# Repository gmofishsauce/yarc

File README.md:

# YARC - Yet Another Retro Computer

## Overview

YARC is a homebrew CPU and computer design implemented in a retro style.
Work on YARC started in April 2021. The initial concept was an 8-bit
computer with a 16-bit multiplexed address/data bus and extensive
pipelining.

In December 2021, the design changed to a 16-bit computer with separate
address and data busses, minimal pipelining, four general registers, an
8-bit-wide/2-cycle ALU, and two hardware stacks. In short, a general
register machine with specific concessions to the efficient implementation
of Charles Moore's FORTH programming language.

Most recently, I decided not to build the stack hardware and to instead
focus on developing the basic instruction set using two of the four
registers for PC and SP. I plan to write a translator for a small subset
of web assembler to YARC machine language (an "AoT" in their terminology,
ahead-of-time compiler). This will allow me to program the YARC in a small
subset any language that can target WASM--like Gnu C or Golang--rather
than confining YARC programming to the Forth language.

YARC is permanently tethered to a host computer (Mac) through a module
called the "Downloader" (a misnomer, because communication is supported
in both directions between host and YARC). The Downloader is based on a
modern microprocessor (Arduino Nano) which implements serial over USB.

The YARC itself is built from 74HC-series CMOS parts, with a few
out-of-period extensions like 8kx8 static CMOS RAMs.

## NRR - It's Not Really Retro

YARC's architecture resembles the [Data General Nova](https://en.wikipedia.org/wiki/Data_General_Nova) minicomputer. The Nova was introduced in 1969. YARC, like Nova, is mostly built from 7400-series components.

But the YARC is _nothing_ like a 1970s minicomputer. Why not? Let me count the ways...

* **Sophisticated open source design software.** In 1969, "design software" meant a sharp pencil, a [plastic template](https://www.amazon.com/Alvin-TD1279-Electric-Electronic-Template/dp/B000KNLR4A/ref=asc_df_B000KNLR4A/), and an angled table. Now, it means [KiCad](https://www.kicad.org/).
* **Highly integrated, sub-100ns static RAMs.** In 1969, semiconductor memory hadn't happened yet. YARC relies on 8k x 8 static CMOS RAMs with 55ns access times - each chip contains more transistors than an _entire_ Data General Nova. And the original Nova, with core memory, had a 5-microsecond cycle time - about 10x slower than YARC can likely achieve.
* **Universal knowledge base.** In 1969, knowledge about computer design was in the hands of a few experts. Today, a quick search can bring you [this](https://www.godevtool.com/GoasmHelp/usflags.htm) or [this](https://www.righto.com/2013/09/the-z-80-has-4-bit-alu-heres-how-it.html).
* **These aren't the 7400 series components you're looking for.** YARC is built with 74HC-series components. These have better noise margins, controlled edge rates, and far lower power consumption than traditional 7400-series TTL. It's fair to say the 74HC-series wasn't introduced until it was already obsolete!

## What's here?

### [ard](https://github.com/gmofishsauce/yarc/tree/main/ard/yarc_fw) - Arduino code for YARC downloader

Nano IDE (v2.X) project holding C++ code for the Arduino that implements
the "Downloader" (which should be renamed to "System Interface" or something).

### [doc](https://github.com/gmofishsauce/yarc/tree/main/doc) - YARC documentation

Engineering documentation for YARC. No "user documentation" is planned,
but some of the documentation is tersely user-oriented, such as the
document that describes the assembly language.

### [ftz](https://github.com/gmofishsauce/yarc/tree/main/ftz) - Fritz sketches for YARC.

Fritzing is a useful sketchpad for breadboard-based designs but it's
incredibly quirky.  No guarantees anyone will be able to load these
sketches, not to mention modify them.

Fritzing really, *really* wants everything in "``~/Documents/Fritzing``" on
Mac, and on Mac, setting $HOME does not affect the expansion of tilde.
But I found that making "``~/Documents/Fritzing``" a symlink into this repo
works.

### [img](https://github.com/gmofishsauce/yarc/tree/main/img) - Eye candy

Images of Fritzing sketches, KiCad schematics, and the implementation
itself. Allows the schematics and layouts to examined without
installing the apps (KiCad and Fritzing).

### [ki](https://github.com/gmofishsauce/yarc/tree/main/ki) - KiCad schematics

I started using KiCad just after 6.0 came out so if you use an earlier
version, you'll have to upgrade to load the sketches.

### [yarc](https://github.com/gmofishsauce/yarc/tree/main/yarc) - Host software

All the host software is written in Go and tested on darwin-amd64
(Intel-based Mac, not M1) only. The host software is contained in a Cobra
CLI defined here.

### [yasm](https://github.com/gmofishsauce/yarc/tree/main/yasm) - YARC microassembler and assembler source code

The YARC assembler supports definition of the assembly language
mnemonics within the language along with the microcode for each
instruction. So the code in this directory defines the YARC instruction
set.

The assembler itself is invoked by `yarc asm ...` in the host software.

## Problems with YARC

YARC is my first-ever large digital design. It has many issues.

### Messy Control Circuitry

The microcode (writable control store) and ALU (arithmetic/logical unit) of YARC are implemented with RAMs instead of the more common EEROM/EPROM technologies. The RAMs must be "downloaded" with content from the host (Mac) through the Arduino ("downloader") before YARC can start.

This is cool, as I can fundamentally change YARC's behavior without popping ROMs in and out of circuit. But it greatly complicated the design, requiring a "back bus" for writes to ALU and Microcode RAM, additional transceivers, and control circuitry. I made matters much worse by failing to think through the control circuitry in a unified way, instead constructing a bunch of special-purpose control registers.

### Floorplanning Issues

YARC is implemented on 32 large solderless breadboards mounted to four 1' square copper clad boards. At 2' by 2', it has the potential for very long wire runs. I made this situation far worse than necessary by putting controls distribution in the center rather than centralizing data buses and bus transceivers and bringing control signals in from the edges.

### Write timing

Both the main memory RAMs and the 74HC670 devices used for the dual-ported general registers suffer from issues if their address inputs change while their write-enable signals are active (low in both cases). I conceived each bus cycle as "outputs are enabled during first half of clock with clock high, enables go low for second half of clock, and writes are latched at rising edge". Unfortunately, transceivers enables are "enables", and also drive address lines; so their settling time overlaps with the write signal going low. I had to implement delay lines for write clocks in two places.

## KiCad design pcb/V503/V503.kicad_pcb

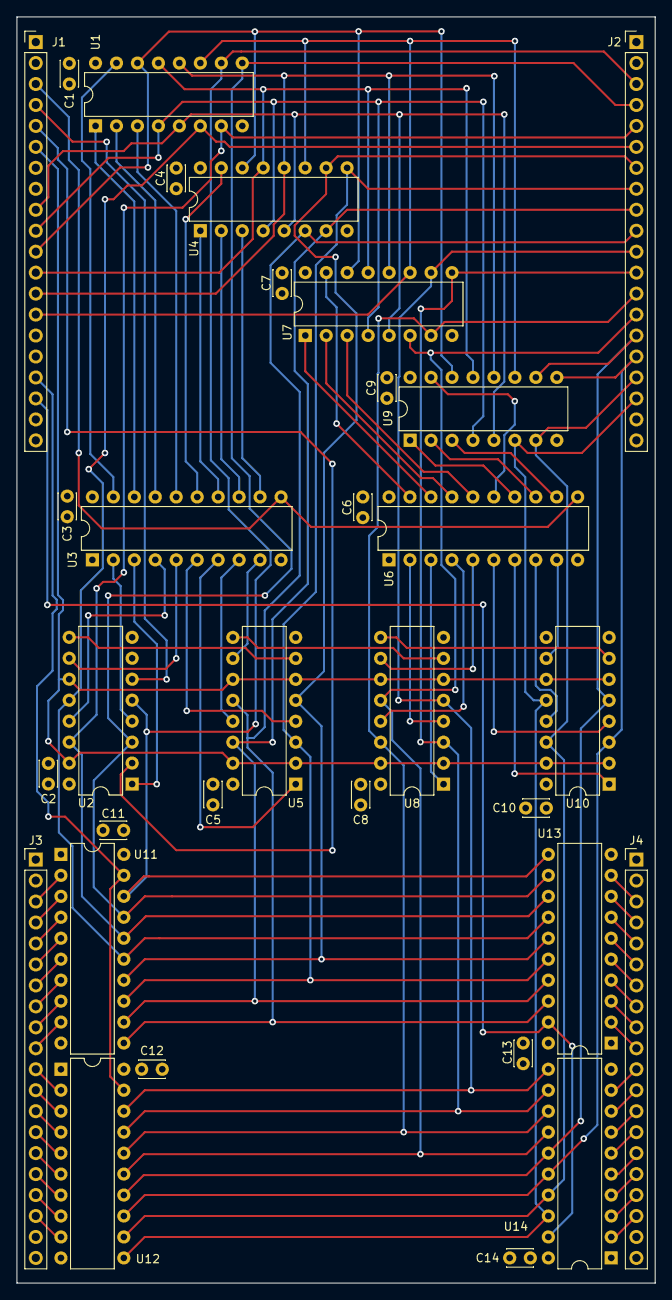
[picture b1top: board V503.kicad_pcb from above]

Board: 4 copper layers, 77.3 x 153.4 mm, 32 parts (0 on the bottom side), 97 nets.

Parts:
C1, C2, C3, C4, C5, C6, C7, C8, C9, C10, C11, C12, C13, C14: C_Small; C_Disc_D3.0mm_W2.0mm_P2.50mm
J1, J2, J3, J4: Conn_01x20_Pin; PinHeader_1x20_P2.54mm_Vertical
U1, U4, U7, U9: 74LS670; DIP-16_W7.62mm
U2, U5, U8, U10: 74LS283; DIP-16_W7.62mm
U3, U6: 74LS574; DIP-20_W7.62mm
U11, U12, U13, U14: 74LS245; DIP-20_W7.62mm

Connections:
ALU0: J3.3, U11.2 (A0)
ALU1: J3.4, U11.3 (A1)
ALU2: J3.5, U11.4 (A2)
ALU3: J3.6, U11.5 (A3)
ALU4: J3.7, U11.6 (A4)
ALU5: J3.8, U11.7 (A5)
ALU6: J3.9, U11.8 (A6)
ALU7: J3.10, U11.9 (A7)
ALU8: J3.11, U12.2 (A0)
ALU9: J3.12, U12.3 (A1)
ALU10: J3.13, U12.4 (A2)
ALU11: J3.14, U12.5 (A3)
ALU12: J3.15, U12.6 (A4)
ALU13: J3.16, U12.7 (A5)
ALU14: J3.17, U12.8 (A6)
ALU15: J3.18, U12.9 (A7)
CO4: U2.9 (C4), U5.7 (C0)
CO8: U5.9 (C4), U8.7 (C0)
CO12: U8.9 (C4), U10.7 (C0)
GND: C1.2, C2.2, C3.2, C4.2, C5.2, C6.2, C7.2, C8.2, C9.2, C10.2, C11.2, C12.2, C13.2, C14.2, J2.1, J2.2, J2.19, J2.20, J4.1, J4.2, J4.19, J4.20, U1.8 (GND), U2.7 (C0), U2.8 (GND), U3.1 (OE), U3.10 (GND), U4.8 (GND), U5.8 (GND), U6.1 (OE), U6.10 (GND), U7.8 (GND), U8.8 (GND), U9.8 (GND), U10.8 (GND), U11.10 (GND), U12.10 (GND), U13.1 (A->B), U13.10 (GND), U14.1 (A->B), U14.10 (GND)
HLD0: U1.15 (D1), U3.19 (Q0)
HLD1: U1.1 (D2), U3.18 (Q1)
HLD2: U1.2 (D3), U3.17 (Q2)
HLD3: U1.3 (D4), U3.16 (Q3)
HLD4: U3.15 (Q4), U4.15 (D1)
HLD5: U3.14 (Q5), U4.1 (D2)
HLD6: U3.13 (Q6), U4.2 (D3)
HLD7: U3.12 (Q7), U4.3 (D4)
HLD8: U6.19 (Q0), U7.15 (D1)
HLD9: U6.18 (Q1), U7.1 (D2)
HLD10: U6.17 (Q2), U7.2 (D3)
HLD11: U6.16 (Q3), U7.3 (D4)
HLD12: U6.15 (Q4), U9.15 (D1)
HLD13: U6.14 (Q5), U9.1 (D2)
HLD14: U6.13 (Q6), U9.2 (D3)
HLD15: U6.12 (Q7), U9.3 (D4)
Ra: J1.9, U1.5 (Ra), U4.5 (Ra), U7.5 (Ra), U9.5 (Ra)
Rb: J1.10, U1.4 (Rb), U4.4 (Rb), U7.4 (Rb), U9.4 (Rb)
SRC2:0: J1.4, U2.6 (B1)
SRC2:1: J1.5, U2.2 (B2)
SRC2:2: J1.6, U2.11 (B4), U2.15 (B3), U5.2 (B2), U5.6 (B1), U5.11 (B4), U5.15 (B3), U8.2 (B2), U8.6 (B1), U8.11 (B4), U8.15 (B3), U10.2 (B2), U10.6 (B1), U10.11 (B4), U10.15 (B3)
SUM0: U2.4 (S1), U3.2 (D0)
SUM1: U2.1 (S2), U3.3 (D1)
SUM2: U2.13 (S3), U3.4 (D2)
SUM3: U2.10 (S4), U3.5 (D3)
SUM4: U3.6 (D4), U5.4 (S1)
SUM5: U3.7 (D5), U5.1 (S2)
SUM6: U3.8 (D6), U5.13 (S3)
SUM7: U3.9 (D7), U5.10 (S4)
SUM8: U6.2 (D0), U8.4 (S1)
SUM9: U6.3 (D1), U8.1 (S2)
SUM10: U6.4 (D2), U8.13 (S3)
SUM11: U6.5 (D3), U8.10 (S4)
SUM12: U6.6 (D4), U10.4 (S1)
SUM13: U6.7 (D5), U10.1 (S2)
SUM14: U6.8 (D6), U10.13 (S3)
SUM15: U6.9 (D7), U10.10 (S4)
SYSADDR0: J2.3, U1.10 (Q1), U2.5 (A1), U11.18 (B0), U13.11 (B7)
SYSADDR1: J2.4, U1.9 (Q2), U2.3 (A2), U11.17 (B1), U13.12 (B6)
SYSADDR2: J2.5, U1.7 (Q3), U2.14 (A3), U11.16 (B2), U13.13 (B5)
SYSADDR3: J2.6, U1.6 (Q4), U2.12 (A4), U11.15 (B3), U13.14 (B4)
SYSADDR4: J2.7, U4.10 (Q1), U5.5 (A1), U11.14 (B4), U13.15 (B3)
SYSADDR5: J2.8, U4.9 (Q2), U5.3 (A2), U11.13 (B5), U13.16 (B2)
SYSADDR6: J2.9, U4.7 (Q3), U5.14 (A3), U11.12 (B6), U13.17 (B1)
SYSADDR7: J2.10, U4.6 (Q4), U5.12 (A4), U11.11 (B7), U13.18 (B0)
SYSADDR8: J2.11, U7.10 (Q1), U8.5 (A1), U12.18 (B0), U14.11 (B7)
SYSADDR9: J2.12, U7.9 (Q2), U8.3 (A2), U12.17 (B1), U14.12 (B6)
SYSADDR10: J2.13, U7.7 (Q3), U8.14 (A3), U12.16 (B2), U14.13 (B5)
SYSADDR11: J2.14, U7.6 (Q4), U8.12 (A4), U12.15 (B3), U14.14 (B4)
SYSADDR12: J2.15, U9.10 (Q1), U10.5 (A1), U12.14 (B4), U14.15 (B3)
SYSADDR13: J2.16, U9.9 (Q2), U10.3 (A2), U12.13 (B5), U14.16 (B2)
SYSADDR14: J2.17, U9.7 (Q3), U10.14 (A3), U12.12 (B6), U14.17 (B1)
SYSADDR15: J2.18, U9.6 (Q4), U10.12 (A4), U12.11 (B7), U14.18 (B0)
SYSCLK: J1.3, U3.11 (Cp), U6.11 (Cp)
SYSDATA0: J4.3, U13.9 (A7)
SYSDATA1: J4.4, U13.8 (A6)
SYSDATA2: J4.5, U13.7 (A5)
SYSDATA3: J4.6, U13.6 (A4)
SYSDATA4: J4.7, U13.5 (A3)
SYSDATA5: J4.8, U13.4 (A2)
SYSDATA6: J4.9, U13.3 (A1)
SYSDATA7: J4.10, U13.2 (A0)
SYSDATA8: J4.11, U14.9 (A7)
SYSDATA9: J4.12, U14.8 (A6)
SYSDATA10: J4.13, U14.7 (A5)
SYSDATA11: J4.14, U14.6 (A4)
SYSDATA12: J4.15, U14.5 (A3)
SYSDATA13: J4.16, U14.4 (A2)
SYSDATA14: J4.17, U14.3 (A1)
SYSDATA15: J4.18, U14.2 (A0)
VCC: C1.1, C2.1, C3.1, C4.1, C5.1, C6.1, C7.1, C8.1, C9.1, C10.1, C11.1, C12.1, C13.1, C14.1, J1.1, J1.2, J1.7, J1.8, J1.15, J1.16, J1.19, J1.20, J3.1, J3.2, J3.19, J3.20, U1.16 (VCC), U2.16 (VCC), U3.20 (VCC), U4.16 (VCC), U5.16 (VCC), U6.20 (VCC), U7.16 (VCC), U8.16 (VCC), U9.16 (VCC), U10.16 (VCC), U11.1 (A->B), U11.20 (VCC), U12.1 (A->B), U12.20 (VCC), U13.20 (VCC), U14.20 (VCC)
Wa: J1.11, U1.14 (Wa), U4.14 (Wa), U7.14 (Wa), U9.14 (Wa)
Wb: J1.12, U1.13 (Wb), U4.13 (Wb), U7.13 (Wb), U9.13 (Wb)
~ALUtoA: J1.17, U11.19 (CE), U12.19 (CE)
~AtoD: J1.18, U13.19 (CE), U14.19 (CE)
~Er: J1.14, U1.11 (~Er), U4.11 (~Er), U7.11 (~Er), U9.11 (~Er)
~Ew: J1.13, U1.12 (~Ew), U4.12 (~Ew), U7.12 (~Ew), U9.12 (~Ew)

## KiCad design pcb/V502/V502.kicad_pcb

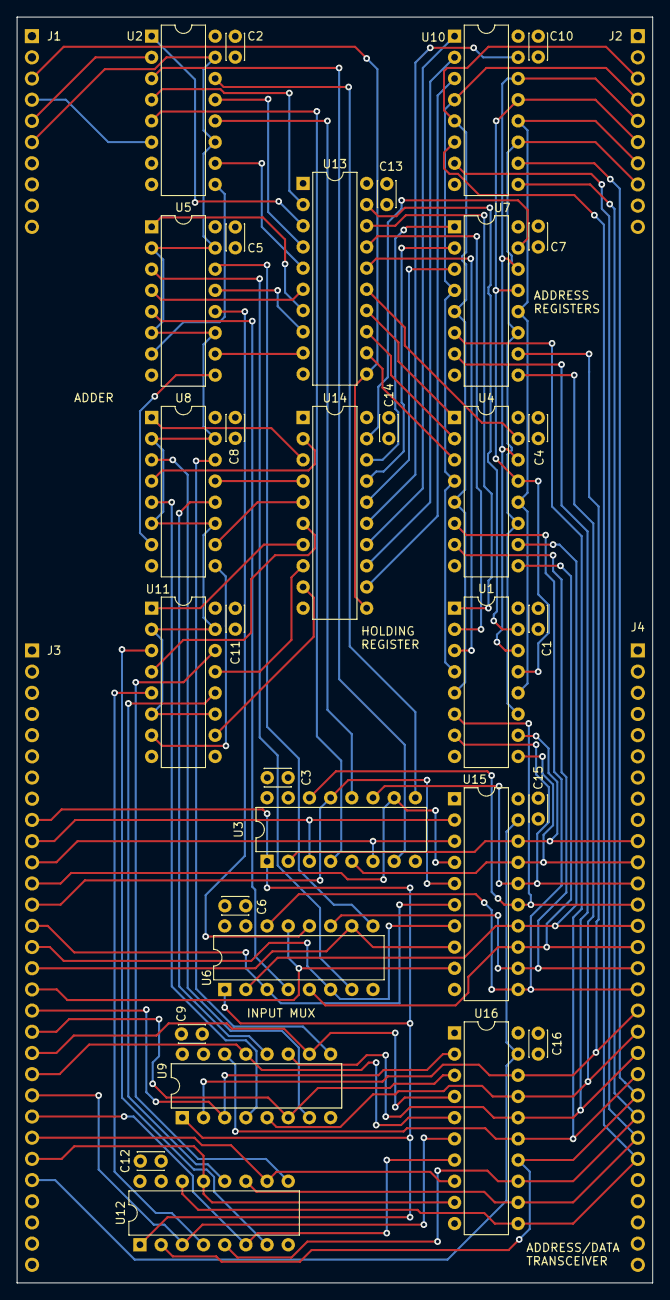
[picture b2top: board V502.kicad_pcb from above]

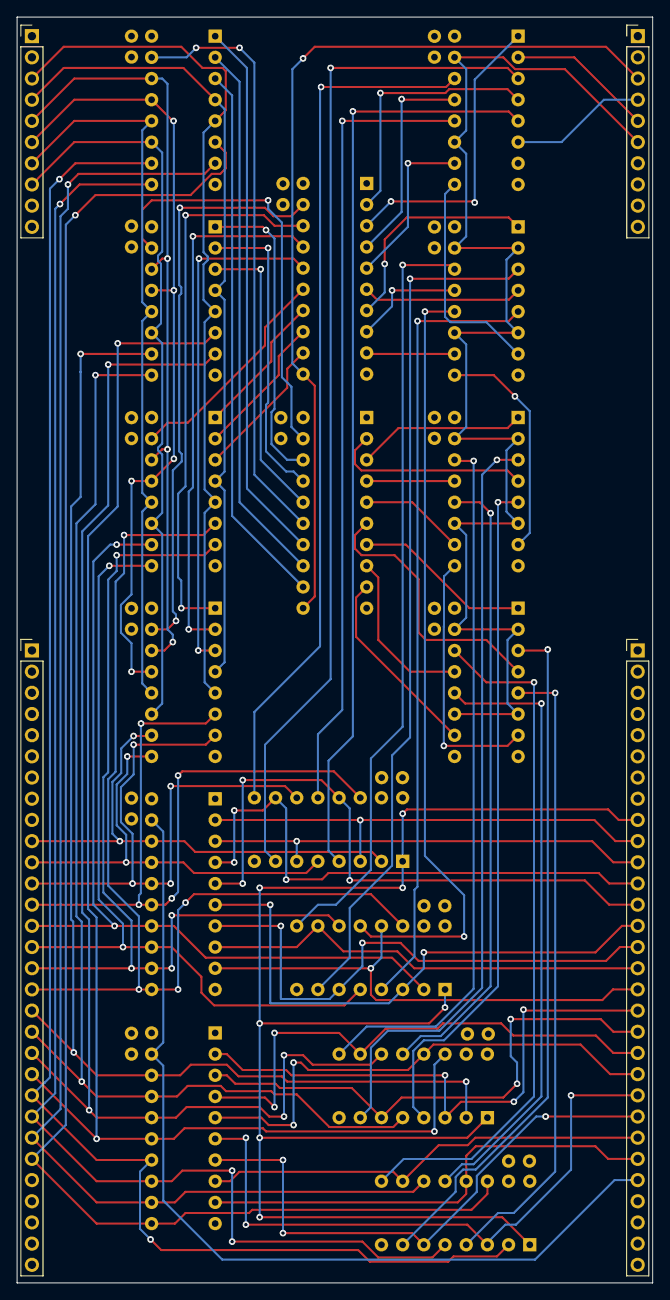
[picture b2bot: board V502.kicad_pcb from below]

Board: 4 copper layers, 76.2 x 151.8 mm, 36 parts (4 on the bottom side), 97 nets.

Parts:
C1, C2, C3, C4, C5, C6, C7, C8, C9, C10, C11, C12, C13, C14, C15, C16: C_Small; C_Disc_D3.0mm_W2.0mm_P2.50mm
J1, J2: Conn_01x10_Pin; PinHeader_1x10_P2.54mm_Vertical
J3, J4: Conn_01x30_Pin; PinHeader_1x30_P2.54mm_Vertical
U1, U4, U7, U10: 74LS670; DIP-16_W7.62mm
U2, U5, U8, U11: 74LS283; DIP-16_W7.62mm
U3, U6, U9, U12: 74LS157; DIP-16_W7.62mm
U13, U14: 74LS574; DIP-20_W7.62mm
U15, U16: 74LS245; DIP-20_W7.62mm

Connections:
A0: U2.5 (A1), U3.4 (Za)
A1: U2.3 (A2), U3.7 (Zb)
A2: U2.14 (A3), U3.9 (Zc)
A3: U2.12 (A4), U3.12 (Zd)
A4: U5.5 (A1), U6.4 (Za)
A5: U5.3 (A2), U6.7 (Zb)
A6: U5.14 (A3), U6.9 (Zc)
A7: U5.12 (A4), U6.12 (Zd)
A8: U8.5 (A1), U9.4 (Za)
A9: U8.3 (A2), U9.7 (Zb)
A10: U8.14 (A3), U9.9 (Zc)
A11: U8.12 (A4), U9.12 (Zd)
A12: U11.5 (A1), U12.4 (Za)
A13: U11.3 (A2), U12.7 (Zb)
A14: U11.14 (A3), U12.9 (Zc)
A15: U11.12 (A4), U12.12 (Zd)
GND: C1.2, C2.2, C3.2, C4.2, C5.2, C6.2, C7.2, C8.2, C9.2, C10.2, C11.2, C12.2, C13.2, C14.2, C15.2, C16.2, J2.1, J2.2, J2.9, J2.10, J4.1, J4.2, J4.3, J4.4, J4.5, J4.6, J4.7, J4.8, J4.9, J4.26, J4.27, J4.28, J4.29, J4.30, U1.8 (GND), U2.7 (C0), U2.8 (GND), U3.8 (GND), U3.15 (E), U4.8 (GND), U5.8 (GND), U6.8 (GND), U6.15 (E), U7.8 (GND), U8.8 (GND), U9.8 (GND), U9.15 (E), U10.8 (GND), U11.8 (GND), U12.8 (GND), U12.15 (E), U13.1 (OE), U13.10 (GND), U14.1 (OE), U14.10 (GND), U15.1 (A->B), U15.10 (GND), U16.1 (A->B), U16.10 (GND)
HLD0: U1.15 (D1), U13.19 (Q0)
HLD1: U1.1 (D2), U13.18 (Q1)
HLD2: U1.2 (D3), U13.17 (Q2)
HLD3: U1.3 (D4), U13.16 (Q3)
HLD4: U4.15 (D1), U13.15 (Q4)
HLD5: U4.1 (D2), U13.14 (Q5)
HLD6: U4.2 (D3), U13.13 (Q6)
HLD7: U4.3 (D4), U13.12 (Q7)
HLD8: U7.15 (D1), U14.19 (Q0)
HLD9: U7.1 (D2), U14.18 (Q1)
HLD10: U7.2 (D3), U14.17 (Q2)
HLD11: U7.3 (D4), U14.16 (Q3)
HLD12: U10.15 (D1), U14.15 (Q4)
HLD13: U10.1 (D2), U14.14 (Q5)
HLD14: U10.2 (D3), U14.13 (Q6)
HLD15: U10.3 (D4), U14.12 (Q7)
unnamed: U2.9 (C4), U5.7 (C0)
unnamed: U5.9 (C4), U8.7 (C0)
unnamed: U8.9 (C4), U11.7 (C0)
Ra: J2.3, U1.5 (Ra), U4.5 (Ra), U7.5 (Ra), U10.5 (Ra)
Rb: J2.4, U1.4 (Rb), U4.4 (Rb), U7.4 (Rb), U10.4 (Rb)
SELDATA: J3.9, U3.1 (S), U6.1 (S), U9.1 (S), U12.1 (S)
SRC2:0: J1.4, U2.6 (B1)
SRC2:1: J1.5, U2.2 (B2)
SRC2:2: J1.6, U2.11 (B4), U2.15 (B3), U5.2 (B2), U5.6 (B1), U5.11 (B4), U5.15 (B3), U8.2 (B2), U8.6 (B1), U8.11 (B4), U8.15 (B3), U11.2 (B2), U11.6 (B1), U11.11 (B4), U11.15 (B3)
SUM0: U2.4 (S1), U13.2 (D0)
SUM1: U2.1 (S2), U13.3 (D1)
SUM2: U2.13 (S3), U13.4 (D2)
SUM3: U2.10 (S4), U13.5 (D3)
SUM4: U5.4 (S1), U13.6 (D4)
SUM5: U5.1 (S2), U13.7 (D5)
SUM6: U5.13 (S3), U13.8 (D6)
SUM7: U5.10 (S4), U13.9 (D7)
SUM8: U8.4 (S1), U14.2 (D0)
SUM9: U8.1 (S2), U14.3 (D1)
SUM10: U8.13 (S3), U14.4 (D2)
SUM11: U8.10 (S4), U14.5 (D3)
SUM12: U11.4 (S1), U14.6 (D4)
SUM13: U11.1 (S2), U14.7 (D5)
SUM14: U11.13 (S3), U14.8 (D6)
SUM15: U11.10 (S4), U14.9 (D7)
SYSADDR0: J4.10, U1.10 (Q1), U3.2 (I0a), U15.18 (B0)
SYSADDR1: J4.11, U1.9 (Q2), U3.5 (I0b), U15.17 (B1)
SYSADDR2: J4.12, U1.7 (Q3), U3.11 (I0c), U15.16 (B2)
SYSADDR3: J4.13, U1.6 (Q4), U3.14 (I0d), U15.15 (B3)
SYSADDR4: J4.14, U4.10 (Q1), U6.2 (I0a), U15.14 (B4)
SYSADDR5: J4.15, U4.9 (Q2), U6.5 (I0b), U15.13 (B5)
SYSADDR6: J4.16, U4.7 (Q3), U6.11 (I0c), U15.12 (B6)
SYSADDR7: J4.17, U4.6 (Q4), U6.14 (I0d), U15.11 (B7)
SYSADDR8: J4.18, U7.10 (Q1), U9.2 (I0a), U16.18 (B0)
SYSADDR9: J4.19, U7.9 (Q2), U9.5 (I0b), U16.17 (B1)
SYSADDR10: J4.20, U7.7 (Q3), U9.11 (I0c), U16.16 (B2)
SYSADDR11: J4.21, U7.6 (Q4), U9.14 (I0d), U16.15 (B3)
SYSADDR12: J4.22, U10.10 (Q1), U12.2 (I0a), U16.14 (B4)
SYSADDR13: J4.23, U10.9 (Q2), U12.5 (I0b), U16.13 (B5)
SYSADDR14: J4.24, U10.7 (Q3), U12.11 (I0c), U16.12 (B6)
SYSADDR15: J4.25, U10.6 (Q4), U12.14 (I0d), U16.11 (B7)
SYSCLK: J1.3, U13.11 (Cp), U14.11 (Cp)
SYSDATA0: J3.10, U3.3 (I1a), U15.2 (A0)
SYSDATA1: J3.11, U3.6 (I1b), U15.3 (A1)
SYSDATA2: J3.12, U3.10 (I1c), U15.4 (A2)
SYSDATA3: J3.13, U3.13 (I1d), U15.5 (A3)
SYSDATA4: J3.14, U6.3 (I1a), U15.6 (A4)
SYSDATA5: J3.15, U6.6 (I1b), U15.7 (A5)
SYSDATA6: J3.16, U6.10 (I1c), U15.8 (A6)
SYSDATA7: J3.17, U6.13 (I1d), U15.9 (A7)
SYSDATA8: J3.18, U9.3 (I1a), U16.2 (A0)
SYSDATA9: J3.19, U9.6 (I1b), U16.3 (A1)
SYSDATA10: J3.20, U9.10 (I1c), U16.4 (A2)
SYSDATA11: J3.21, U9.13 (I1d), U16.5 (A3)
SYSDATA12: J3.22, U12.3 (I1a), U16.6 (A4)
SYSDATA13: J3.23, U12.6 (I1b), U16.7 (A5)
SYSDATA14: J3.24, U12.10 (I1c), U16.8 (A6)
SYSDATA15: J3.25, U12.13 (I1d), U16.9 (A7)
VCC: C1.1, C2.1, C3.1, C4.1, C5.1, C6.1, C7.1, C8.1, C9.1, C10.1, C11.1, C12.1, C13.1, C14.1, C15.1, C16.1, J1.1, J1.2, J1.7, J1.8, J1.9, J1.10, J3.1, J3.2, J3.3, J3.4, J3.5, J3.6, J3.7, J3.8, J3.27, J3.28, J3.29, J3.30, U1.16 (VCC), U2.16 (VCC), U3.16 (VCC), U4.16 (VCC), U5.16 (VCC), U6.16 (VCC), U7.16 (VCC), U8.16 (VCC), U9.16 (VCC), U10.16 (VCC), U11.16 (VCC), U12.16 (VCC), U13.20 (VCC), U14.20 (VCC), U15.20 (VCC), U16.20 (VCC)
Wa: J2.5, U1.14 (Wa), U4.14 (Wa), U7.14 (Wa), U10.14 (Wa)
Wb: J2.6, U1.13 (Wb), U4.13 (Wb), U7.13 (Wb), U10.13 (Wb)
~AtoD: J3.26, U15.19 (CE), U16.19 (CE)
~Er: J2.8, U1.11 (~Er), U4.11 (~Er), U7.11 (~Er), U10.11 (~Er)
~Ew: J2.7, U1.12 (~Ew), U4.12 (~Ew), U7.12 (~Ew), U10.12 (~Ew)

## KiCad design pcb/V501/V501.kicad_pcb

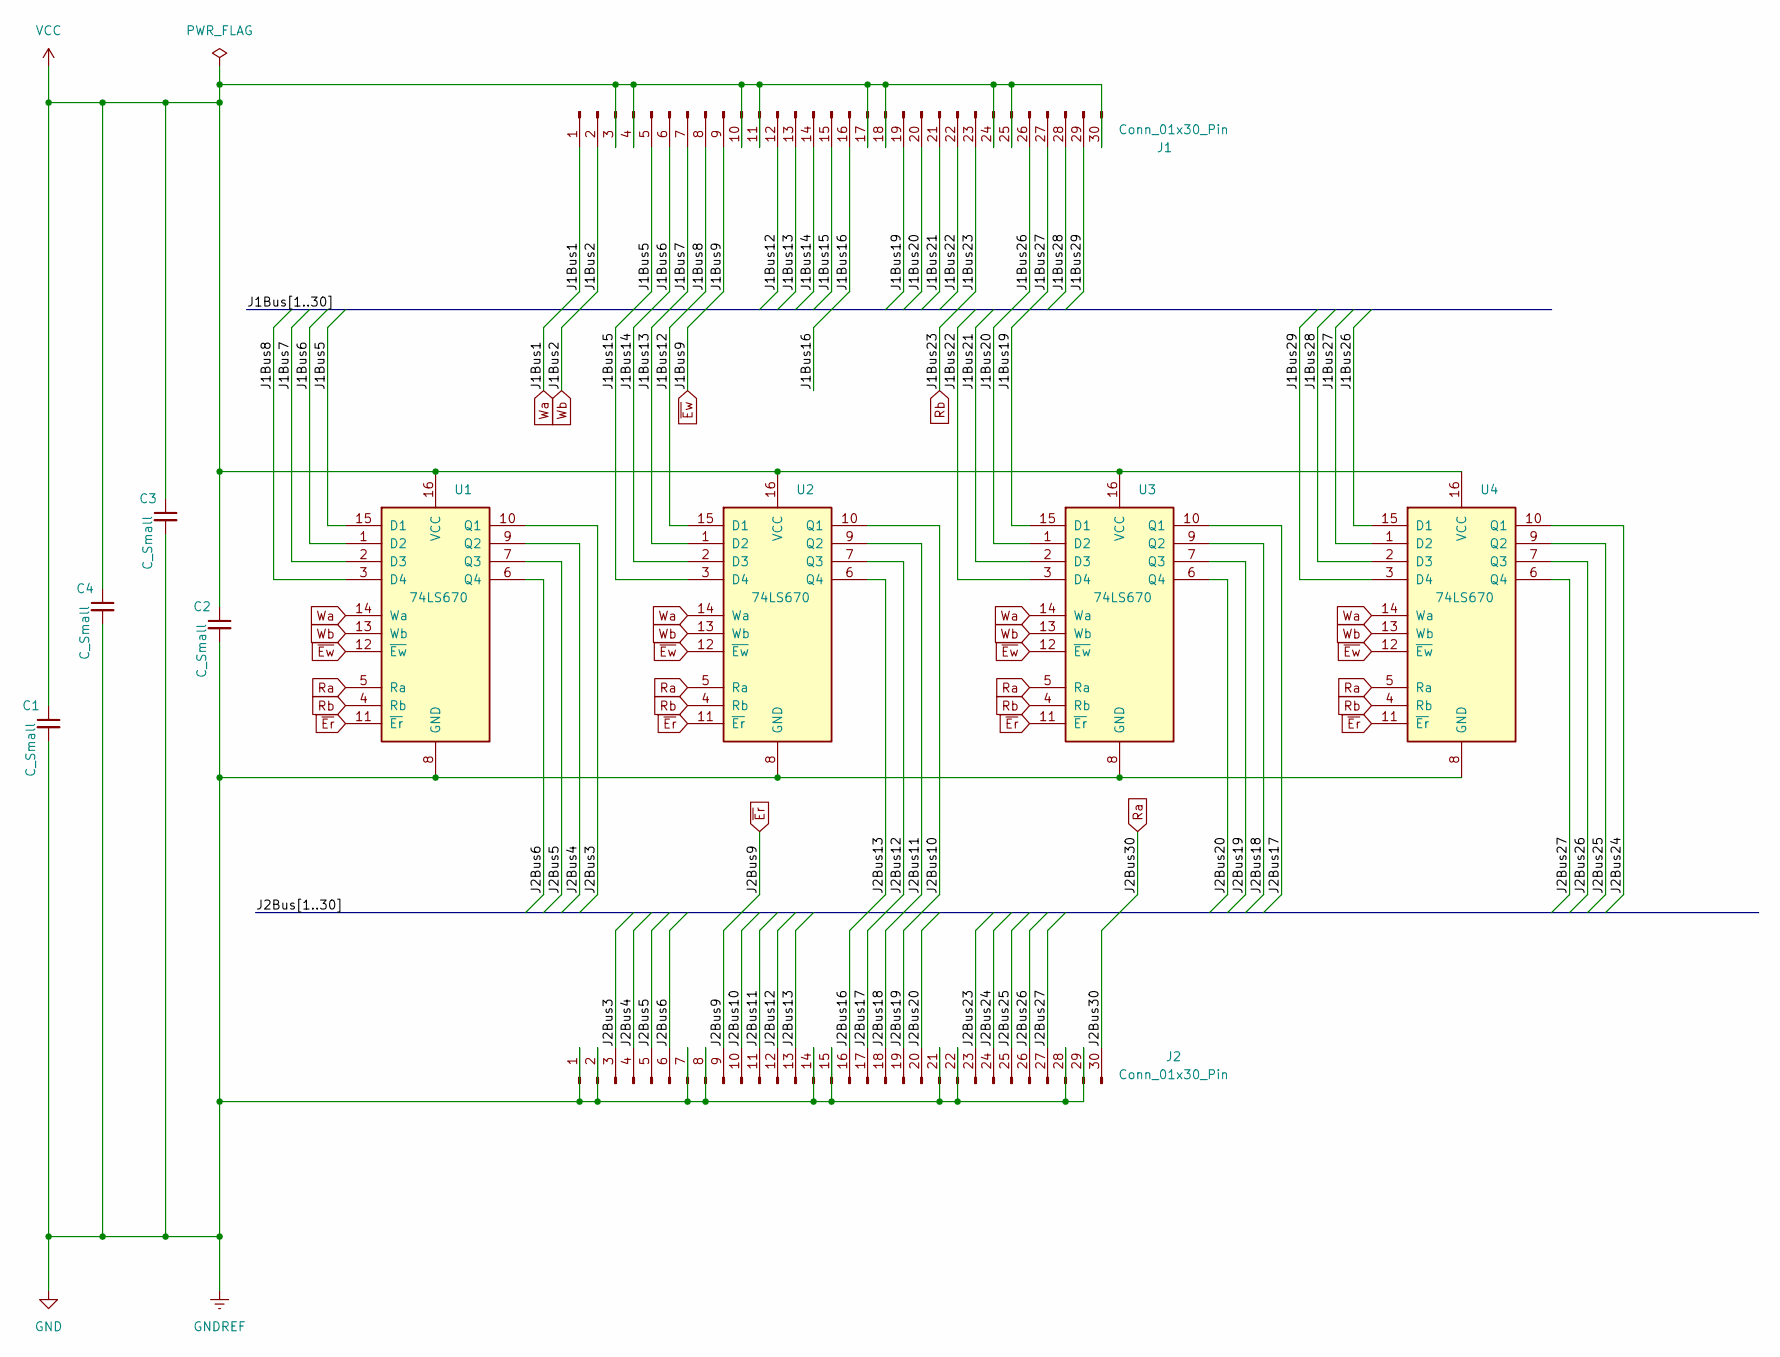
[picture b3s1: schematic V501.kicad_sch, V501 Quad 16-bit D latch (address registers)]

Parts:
C1, C2, C3, C4: C_Small; C_Disc_D5.0mm_W2.5mm_P2.50mm
J1, J2: Conn_01x30_Pin; PinHeader_1x30_P2.54mm_Vertical
U1, U2, U3, U4: 74LS670; DIP-16_W7.62mm

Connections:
/J1Bus5: J1.5, U1.15 (D1)
/J1Bus6: J1.6, U1.1 (D2)
/J1Bus7: J1.7, U1.2 (D3)
/J1Bus8: J1.8, U1.3 (D4)
/J1Bus12: J1.12, U2.15 (D1)
/J1Bus13: J1.13, U2.1 (D2)
/J1Bus14: J1.14, U2.2 (D3)
/J1Bus15: J1.15, U2.3 (D4)
/J1Bus16: J1.16
/J1Bus19: J1.19, U3.15 (D1)
/J1Bus20: J1.20, U3.1 (D2)
/J1Bus21: J1.21, U3.2 (D3)
/J1Bus22: J1.22, U3.3 (D4)
/J1Bus26: J1.26, U4.15 (D1)
/J1Bus27: J1.27, U4.1 (D2)
/J1Bus28: J1.28, U4.2 (D3)
/J1Bus29: J1.29, U4.3 (D4)
/J2Bus3: J2.3, U1.10 (Q1)
/J2Bus4: J2.4, U1.9 (Q2)
/J2Bus5: J2.5, U1.7 (Q3)
/J2Bus6: J2.6, U1.6 (Q4)
/J2Bus10: J2.10, U2.10 (Q1)
/J2Bus11: J2.11, U2.9 (Q2)
/J2Bus12: J2.12, U2.7 (Q3)
/J2Bus13: J2.13, U2.6 (Q4)
/J2Bus16: J2.16
/J2Bus17: J2.17, U3.10 (Q1)
/J2Bus18: J2.18, U3.9 (Q2)
/J2Bus19: J2.19, U3.7 (Q3)
/J2Bus20: J2.20, U3.6 (Q4)
/J2Bus23: J2.23
/J2Bus24: J2.24, U4.10 (Q1)
/J2Bus25: J2.25, U4.9 (Q2)
/J2Bus26: J2.26, U4.7 (Q3)
/J2Bus27: J2.27, U4.6 (Q4)
GND: C1.2, C2.2, C3.2, C4.2, J2.1, J2.2, J2.7, J2.8, J2.14, J2.15, J2.21, J2.22, J2.28, J2.29, U1.8 (GND), U2.8 (GND), U3.8 (GND), U4.8 (GND)
Ra: J2.30, U1.5 (Ra), U2.5 (Ra), U3.5 (Ra), U4.5 (Ra)
Rb: J1.23, U1.4 (Rb), U2.4 (Rb), U3.4 (Rb), U4.4 (Rb)
VCC: C1.1, C2.1, C3.1, C4.1, J1.3, J1.4, J1.10, J1.11, J1.17, J1.18, J1.24, J1.25, J1.30, U1.16 (VCC), U2.16 (VCC), U3.16 (VCC), U4.16 (VCC)
Wa: J1.1, U1.14 (Wa), U2.14 (Wa), U3.14 (Wa), U4.14 (Wa)
Wb: J1.2, U1.13 (Wb), U2.13 (Wb), U3.13 (Wb), U4.13 (Wb)
~Er: J2.9, U1.11 (~Er), U2.11 (~Er), U3.11 (~Er), U4.11 (~Er)
~Ew: J1.9, U1.12 (~Ew), U2.12 (~Ew), U3.12 (~Ew), U4.12 (~Ew)

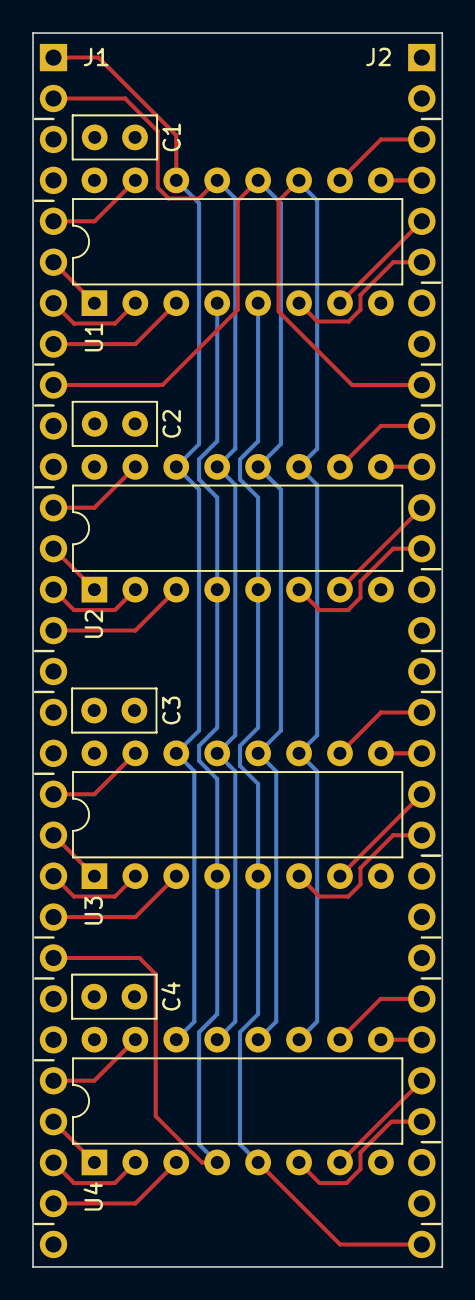
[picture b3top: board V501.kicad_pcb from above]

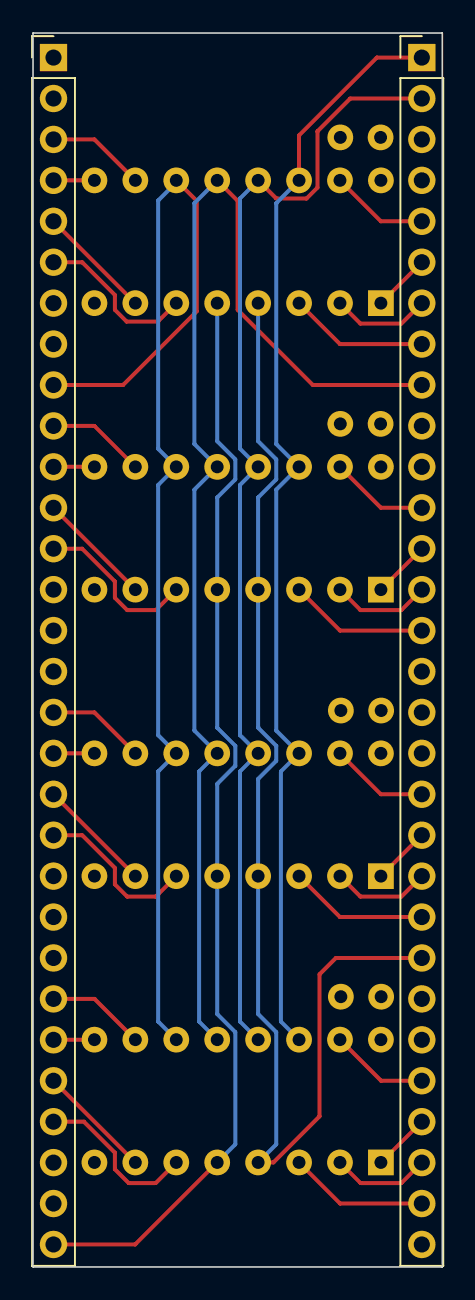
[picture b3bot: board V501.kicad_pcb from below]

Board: 4 copper layers, 25.4 x 76.6 mm, 10 parts (2 on the bottom side), 40 nets.

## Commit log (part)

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2022-04-04 Add license and experiment with README formatting
2022-04-10 Ongoing development
2022-04-17 Add gitignore. Update memory read signal. Update memory transceiver direction control. Many routing improvements.
2022-04-24 Minor wiring updates and reorg some software
2022-04-25 Package naming experimet - must push
2022-04-27 Implement 'yarc host' (former 'ser' command)
2022-04-29 Attempting to fix table formatting
2022-04-29 First work on Assembler doc
2022-05-05 yasm code with seg fault
2022-05-16 Remove old Go code now in yarc/
2022-05-22 Lexer is pretty functional now
2022-06-14 Updates - 32k RAM is working
2022-06-19 Fix a couple of errors
2022-06-22 Fix problem in unread byte. Implement include and bitfield builtins.
2022-06-24 Implement a hacky opcode handler and some tests that don't pass
2022-06-26 All the basic builtins function
2022-07-02 Further polishing on the assembler
2022-07-05 Add microcode engine to KiCad. Minor updates to README.
2022-07-06 Significant progress on microcode schematic. Minor improvements to MemorySystem.md.
2022-07-08 Populate img/2022-07-07 directory
2022-08-10 Much work on ALU and registers
2022-08-19 Add MEM_EN# fix to arch.yasm, KiCad, and Fritzing
2022-08-21 Partway through Nano-specific optimizations to ard/port_task.h
2022-08-23 Change to Nano-specific functions. Code does not work.
2022-08-25 Continue transition to Nano-specific fast registers
2022-08-25 Remove last vestigates of Arduino logical pin definitions
2022-08-28 Nano IR clock and mem enable changes documented in Ki, Ftz, and port_task.h
2022-08-31 Part way through shadow MCR update. Create handlers.go in yarc host command.
2022-09-08 Major cleanup of port_task.h (again) and minor changes to design
2022-09-09 Fix another couple of bus in ard code. Add code for testing microcode control register. Remove tabs from yasm files.
2022-09-11 Documentary updates
2022-09-19 Changes for UCR support. Not debugged. Minor updates to microcode engine layout.
2022-09-20 In the midst of implementing service requests from Nano
2022-09-23 Results of go mod tidy and latest Arduino code
2022-09-23 Change from submodules to packages
2022-09-24 omg, it seems to work
2022-09-30 Ongoing development of microcode control logic
2022-10-01 Implement writeBytesToSlice() and update the microcode layout in ftz with latest
2022-10-07 Ongoing development of registers and ALU
2022-10-09 Three new parts and two new sketches in Fritzing
2022-10-19 Minor updates. WCS content is not printed.
2022-11-05 Ongoing development of ALU and registers
2022-11-18 Updates to ISA doc. Matching corrections to arch.yasm. Flags layout in Ftz.
2022-11-26 Cleanup and complete Nano serial rewrite. Increase max delay on host side.
2022-12-03 Ongoing debugging
2022-12-04 Protocol version 5 - adds write and read slice
2022-12-07 Fix UCR wiring error in software. Fix microcode assembler and dump code. Minor updates to microcode (yasm).
2022-12-23 All the changes related to the mid-December 2022 K register problem
2022-12-31 The simplest microcode editor that could possibly work
2023-01-07 Assign part labels (U-numbers) in KiCad and start adding them to Fritzing layouts
2023-01-07 Add empty Cost (Continuous Self Test) task to Nano firmware
2023-01-15 Delay task and microcode basic test debugged and believed working
2023-01-27 Finally debugged the 16-bit memory test. No hardware issues.
2023-02-05 Change MCR update methods to functional style and get rid of the shadow register
2023-02-07 Successfully write and read a register in the temporary AnyReset hook
2023-02-13 Write microcode documentation
2023-02-17 Flags development and implement memory fix. Firmware not updated to match the memory fix.
2023-02-18 Startup-time register loopback test passes
2023-02-19 Comment out broken startup code and implement memBasicTest in COST tests
2023-02-21 Add ALU generator and move results writer to a separate file
2023-02-27 Further development of ALU controls
2023-03-05 Significant but incomplete improvements to register COST test
2023-03-08 Finish gold plating the COST test for register access
2023-03-08 Ongoing development of ALU and Flags. Construction start.
2023-03-10 Various corrections and minor improvements
2023-03-14 Remove ALU RAM write from Nano after HW change
2023-03-14 Redesign of ALU control logic
2023-03-24 Interim commit - splitting out YARC functions into new files yarc_utils.h and yarc_decls.h
2023-03-24 Fix longstanding 'lost return or ^D' problem by not recreating the standard input stream. Also fix the 'lost panic' problem by not creating a new session until the user agrees.
2023-03-25 Add a reset message
2023-03-29 Add the ACN mini-bus which can come from the instruction bits 11:8 or from the microcode bits 23:20. It selects the ALU operation and the condition codes.
2023-03-29 Update microcode editor with latest hardware changes
2023-03-30 Discovered that ACN mux was already drawn on another sheet of the schematic - fixed. Added ACN control bit to microcode. Ongoing cleanup: replaced acronym RSW with RCW in assembly language.
2023-04-02 Additional corrections found during wiring
2023-04-02 Condition and ALU control wiring complete.
2023-04-05 Ongoing corrections. Document the Nano's sysbus enable control for the first time.
2023-04-05 There is now a single interface to writing microcode and it's a little faster. Also removed WriteFlags() test loop from startup code now that it's complete. COST passes.
2023-04-11 Implement run and stop COST serial commands. Correct SetK serial command. Remove unimplemeted stop and start clock serial commands. Protocol now version 7. Minor changes to hardware design.
2023-04-19 Minor corrections to signal naming in memory controller
2023-04-19 Clean up code and reenable COST test. Loop removed from startup.
2023-04-20 Remove -w from gcc, which was inhibiting all warnings. Fix the resulting warnings. Most serious were in the serial task, where there were some returns without arguments where the value was used.
2023-04-20 Improve flags test (so far as possible without the ALU)
2023-04-26 Partial implementation of download
2023-05-04 Add support for ACN MUX
2023-05-04 Interim commit with wiring complete. Partial implementation of ALU RAM read/write. Flags test in COST is failing due to HW updates.
2023-05-07 Implement test for ALU RAM and temporarily disable part of flags test
2023-05-07 Add comments about upcoming changes for protocol v8
2023-05-08 Interim code complete on the version 8 protocol changes. All the old code is still present for reference but commented out
2023-05-11 Complete rewrite of upper protocol code. Latest changes untested.
2023-05-12 Clean up printfs only
2023-05-13 Overrun problem addressed. Memory write performance improved. Obsolete code deleted.
2023-05-16 Add ALU RAM read and write protocol commands. Improve COST test for ALU RAM and reduce intertest delay. Improve argument verification; fix boundary checks against END_MEM.
2023-05-17 Document ALU RAM write clock delay line (fix for ALU RAM write issue)
2023-05-17 Improve downloader slightly during performance experiments
2023-05-20 A few improvements to the microassembler web page. Remove existing microcode definitions from yasm as they are obsolete.
2023-05-21 Modest reorganization of reset code. Implement run, stop, get bus interface register, and do single cycle commands to YARC
2023-05-22 Labels can be defined, now, in the assembler, but not yet used.
2023-05-23 Clean up label definition code in prep for implementation of jumps and branches
2023-05-24 Fix the tests, such as they are.
2023-05-26 (Hopefully the final) interim commit - label implementation for assembler
2023-05-27 Convert code generation entirely to metasymbols
2023-05-30 correct internalRunYARC() in SerialTask
2023-05-30 Minor changes to exercise immediate byte and immediate word metasymbols
2023-06-02 Fix download bug (sending incorrect opcode byte). Leave commented-out microcode slice verify and print code.
2023-06-03 Normalize symbol naming between ued and yasm
2023-06-04 Protocol V9. Add Clock Control command.
2023-06-04 Implement ClockCtl (0xE4) on the host side and fix a bug on the Nano side.
2023-06-07 Add support for immediate byte and word move to memory. Add the .rt (register target) fixup for the low-order two bits of the opcode. Add microcode for the 8 mvi instructions. Correct bounds on value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
2023-06-15 Comments and minor cleanups only - no significant functional changes
2023-06-15 Cleanups on the way to first execution - no significant functional changes
2023-06-17 Implement register store indirect opcode and enhance startup test code.
2023-06-19 Change initialization pattern for memory
2023-06-19 Fix arithmetric error converting bytes to int16s
2023-06-19 Begin markdown conversion of serial spec document
2023-06-20 Added content to README
2023-06-20 Create image directory for latest images
2023-06-20 Add PDF containing images of KiCad schematic
2023-06-20 Improve microcode and assembly language documentation
2023-06-23 Set general registers to distinct values for testing. Add long running task detection to task runner.
2023-06-23 Microcode development.
2023-06-26 Protocol version 11. Add debug command to serial spec. Update protogen. Implement debug command db 1 in both host software and Nano firmware. Fix bug where ReadMem16() and WriteMem16() were being cal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
2023-06-27 Modify the lexer to allow @ and , as white space when between tokens. Add more microde for move instructions. Modify the boot (test) code to use the new instructions and new assembler features.
2023-06-29 Fix ALU content generator to handle carry correctly for ADD. Support optional arguments for clock control and initial register values in runYarc()
2023-07-01 Add a test for WriteCheckALU(). Unlike other COST tests, it panics if it fails.
2023-07-01 Fix test - yet another non-hardware problem
2023-07-02 Re-enable the '.acn' fixup which is used to specify the condition on a branch instruction
2023-07-03 Additional work to normalize and develop instruction set (ISA.md) and bring microcode implementation in line. No new functionality.
2023-07-04 Create .rs (r0 or r1) specifier and refactor some code for processing similar directives
2023-07-06 Add very involved memory checker in search for the 0x2000 problem. Also define byte and ushort as types unsigned char and unsigned short.
2023-07-07 Complete the new memclean test and reenable all the other COST tests.
2023-07-08 Add a very limited '.scope/.endscope' directive to the assembly language to reduce the symbol pollution caused by the microcode being in-line with the assembly language.
2023-07-09 More changes to ISA document and tune up opcode definitions to match. Remove an old file.
2023-07-29 This directory may be a result of upgrading to KiCad v7.
2023-07-29 Add V501, an 84-style module with four 16-bit registers (sadly, really latches)
2023-07-31 Begin layout of full addressing unit
2023-08-03 V502 is complete. Freezing it permanently.
2023-08-04 Clean up clearances, run DRC and ERC, and generate Gerbers. Tape out.
2023-08-06 Update ISA for new index registers
2023-08-06 KiCad cleanup - no functional changes.
2023-08-06 Clean up .gitignore
2023-08-09 Continuing cleanup of schematic
2023-08-11 Schematic for addressing unit is complete and all ERC violations addressed
2023-08-14 Minor cleanups and clarifications on the way to major revision
2023-08-16 Normalize ALU and new addressing symbols across web-page microassembler, assembler source, and ISA documentation.
2023-08-17 Add README file
2023-08-21 Development checkpoint
2023-08-21 Development checkpoint. Everything is positioned, grid removed, code beautified.
2023-08-23 Development checkpoint. Additional flow arrows.
2023-09-24 Clean up and improve power on tests
2023-09-27 Improve mandatory startup testing and LED feedback
2023-09-30 Make main schematic match V503 schematic control signal naming and minor layout cleanup
2023-09-30 Add new fields rcw_routing=rcw_normal sysaddr_src=addr_gr (default values) to all K1 byte definitions
2023-10-01 Adjust ldif and mvr opcodes and clean up detritus at end of file
2023-10-04 Simplify test. It's possible this will be YARC's last ever commit.
2024-02-05 Fix image file location
2024-05-28 Continuing work on Chiptester schematic (no changes to YARC)
2024-06-01 Chiptester design roughly complete
2024-06-13 Update chiptester to match small wiring fixes from KiCad
